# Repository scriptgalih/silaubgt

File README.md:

# Library

```python
https://github.com/circuitar/Dimmer
http://www.rinkydinkelectronics.com/library.php?id=47
https://github.com/sparkfun/SparkFun_BME280_Arduino_Library/tree/master/src
https://github.com/claws/BH1750
https://playground.arduino.cc/Code/EEPROMWriteAnything/
```

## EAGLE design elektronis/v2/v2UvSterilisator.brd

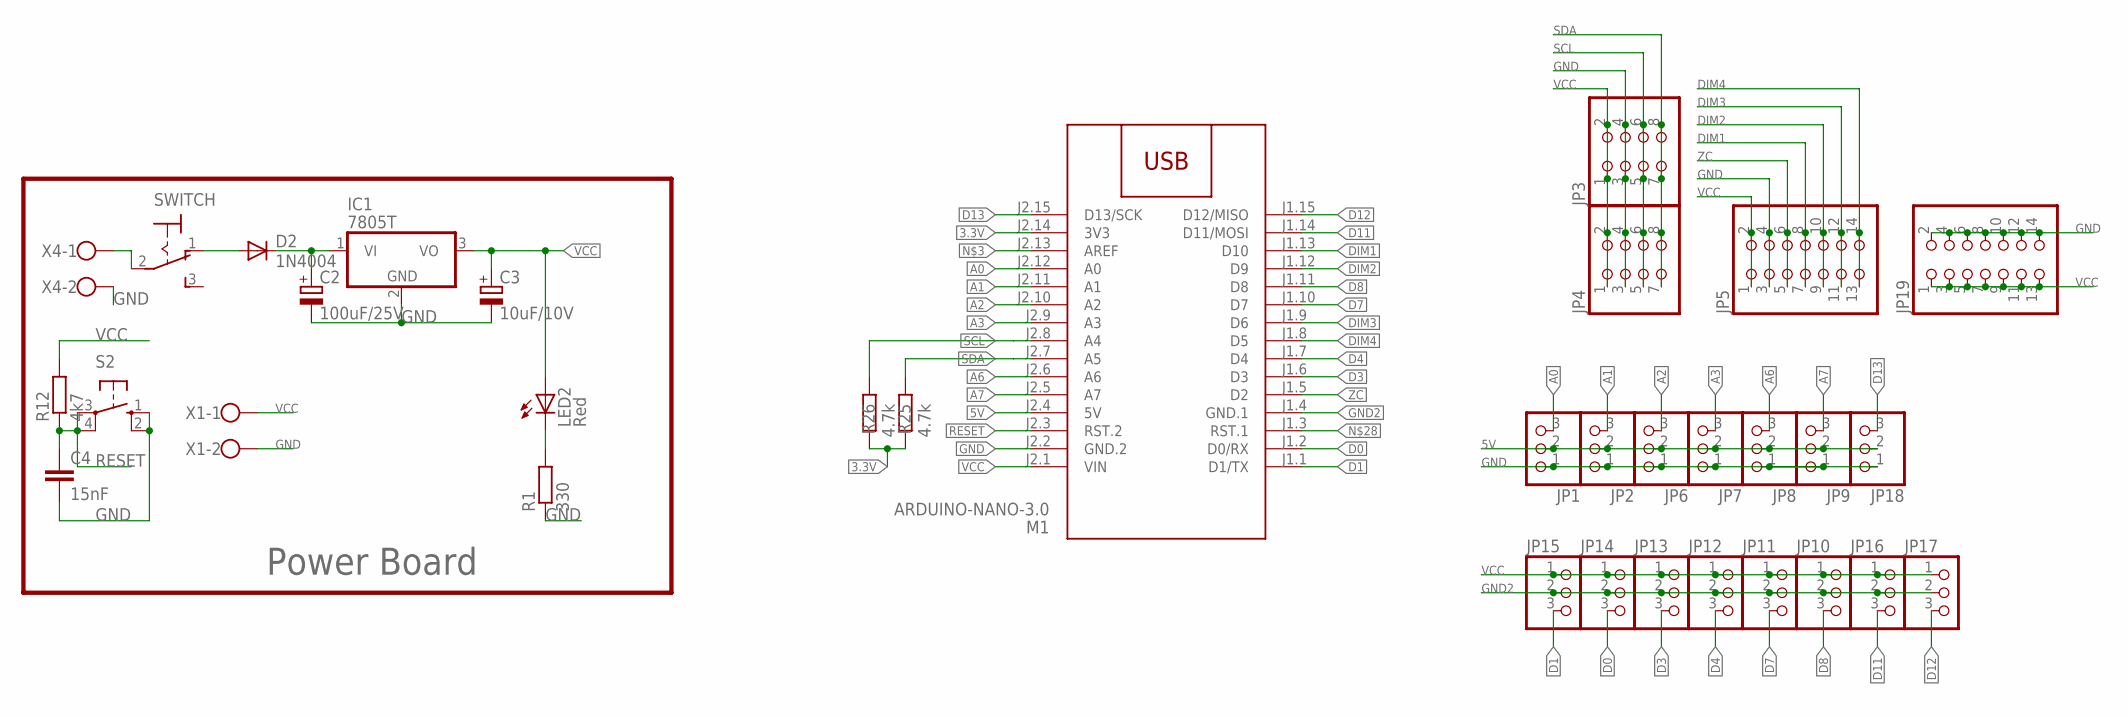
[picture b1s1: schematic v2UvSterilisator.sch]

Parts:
C2: 100uF/25V; E5-8,5
C3: 10uF/10V; E5-8,5
C4: 15nF; C0805
D2: 1N4004; DO41-10
IC1: 7805T; TO220H
JP1, JP2, JP6, JP7, JP8, JP9, JP10, JP11, JP12, JP13, JP14, JP15, JP16, JP17, JP18: PINHD-1X3; 1X03
JP3, JP4: PINHD-2X4; 2X04
JP5, JP19: PINHD-2X7; 2X07
LED2: Red; LED3MM
M1: ARDUINO-NANO-3.0
R1: 330; R1206
R12: 4k7; R1206
R25, R26: 4.7k; R1206
S2: 10-XX; B3F-10XX
SWITCH: M9040P
X1, X4: W237-102

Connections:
3.3V: M1.J2.14 (3V3), R25.2, R26.2
5V: JP1.2, JP2.2, JP6.2, JP7.2, JP8.2, JP9.2, JP18.2, M1.J2.4 (5V)
12VSWITCH: D2.A, SWITCH.1 (O)
A0: JP1.3, M1.J2.12 (A0)
A1: JP2.3, M1.J2.11 (A1)
A2: JP6.3, M1.J2.10 (A2)
A3: JP7.3, M1.J2.9 (A3)
A6: JP8.3, M1.J2.6 (A6)
A7: JP9.3, M1.J2.5 (A7)
D0: JP14.3, M1.J1.2 (D0/RX)
D1: JP15.3, M1.J1.1 (D1/TX)
D3: JP13.3, M1.J1.6 (D3)
D4: JP12.3, M1.J1.7 (D4)
D7: JP11.3, M1.J1.10 (D7)
D8: JP10.3, M1.J1.11 (D8)
D11: JP16.3, M1.J1.14 (D11/MOSI)
D12: JP17.3, M1.J1.15 (D12/MISO)
D13: JP18.3, M1.J2.15 (D13/SCK)
DIM1: JP5.7, JP5.8, M1.J1.13 (D10)
DIM2: JP5.9, JP5.10, M1.J1.12 (D9)
DIM3: JP5.11, JP5.12, M1.J1.9 (D6)
DIM4: JP5.13, JP5.14, M1.J1.8 (D5)
GND: C2.-, C3.-, C4.2, IC1.2 (GND), JP1.1, JP2.1, JP3.3, JP3.4, JP4.3, JP4.4, JP5.3, JP5.4, JP6.1, JP7.1, JP8.1, JP9.1, JP18.1, JP19.2, JP19.4, JP19.6, JP19.8, JP19.10, JP19.12, JP19.14, M1.J2.2 (GND.2), R1.1, S2.1 (S), S2.2 (S1), X1.2, X4.2
GND2: JP10.2, JP11.2, JP12.2, JP13.2, JP14.2, JP15.2, JP16.2, JP17.2, M1.J1.4 (GND.1)
unnamed: C2.+, D2.C, IC1.1 (VI)
unnamed: LED2.K (C), R1.2
unnamed: SWITCH.2, X4.1
RESET: C4.1, M1.J2.3 (RST.2), R12.1, S2.3, S2.4 (P1)
SCL: JP3.5, JP3.6, JP4.5, JP4.6, M1.J2.8 (A4), R26.1
SDA: JP3.7, JP3.8, JP4.7, JP4.8, M1.J2.7 (A5), R25.1
VCC: C3.+, IC1.3 (VO), JP3.1, JP3.2, JP4.1, JP4.2, JP5.1, JP5.2, JP10.1, JP11.1, JP12.1, JP13.1, JP14.1, JP15.1, JP16.1, JP17.1, JP19.1, JP19.3, JP19.5, JP19.7, JP19.9, JP19.11, JP19.13, LED2.A, M1.J2.1 (VIN), R12.2, X1.1
ZC: JP5.5, JP5.6, M1.J1.5 (D2)

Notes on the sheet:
Power Board

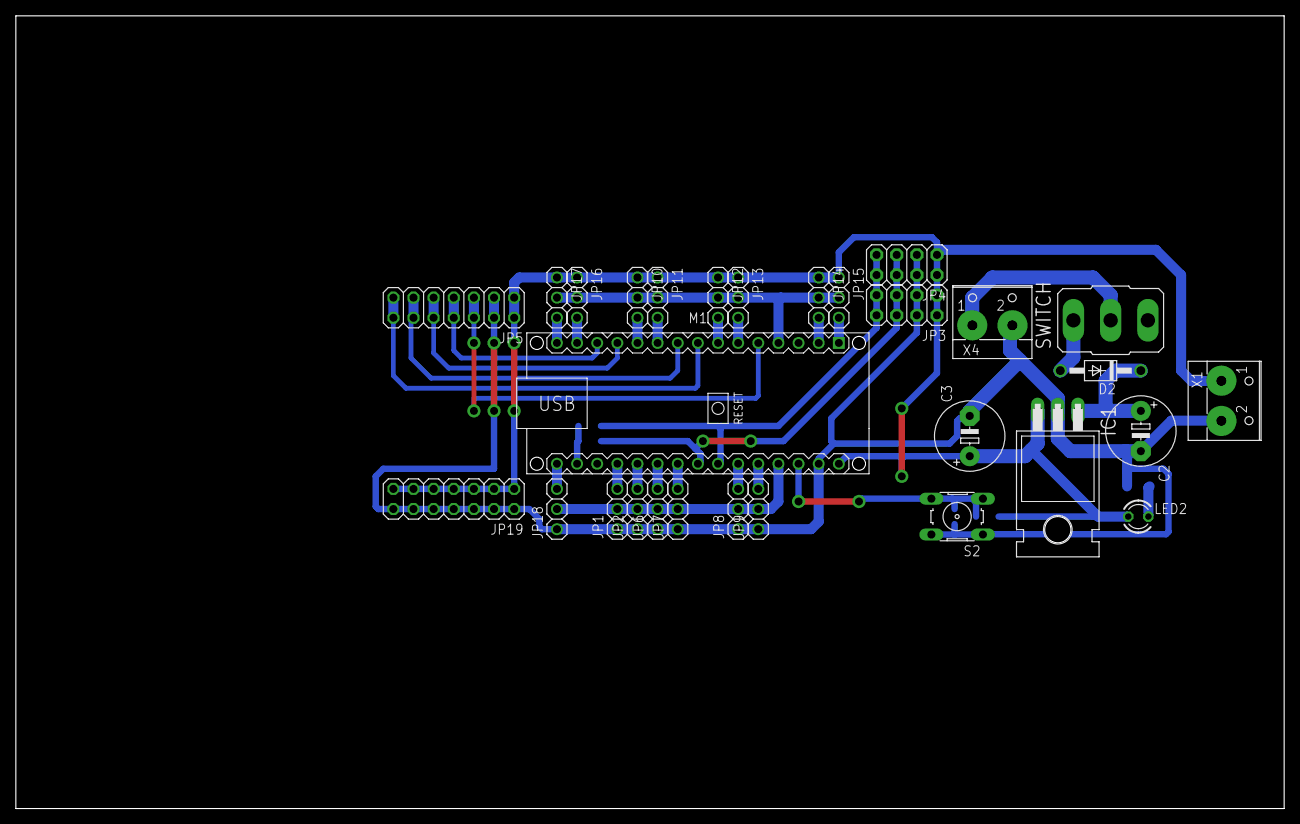
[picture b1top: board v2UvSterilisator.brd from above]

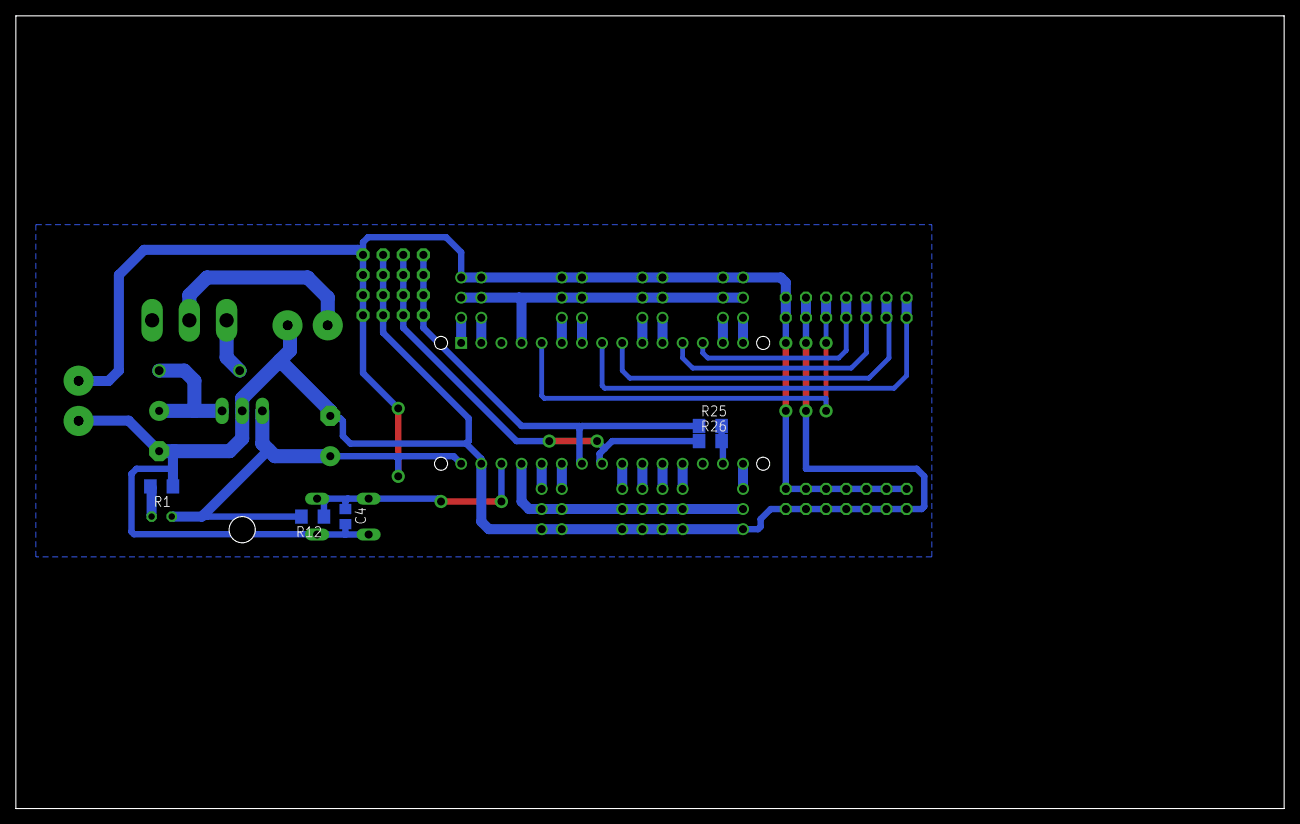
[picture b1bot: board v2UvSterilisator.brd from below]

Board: 2 copper layers, 160.0 x 100.0 mm, 34 parts (5 on the bottom side), 32 nets.

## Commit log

2020-05-12 timer
2020-05-16 add EEPROM
2020-05-16 advance mode_without save
2020-05-16 save advance mode
2020-05-27 new main program (new file)
2020-05-27 fix bug
    timer ngehang
2020-05-28 add custom intensity and door protection
2020-05-28 timer protect
2020-05-28 fix bug adv menu

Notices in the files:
parts and their libraries:
diy-modules: Released under the Creative Commons Attribution 4.0 International License: http://creativecommons.org/licenses/by/4.0
